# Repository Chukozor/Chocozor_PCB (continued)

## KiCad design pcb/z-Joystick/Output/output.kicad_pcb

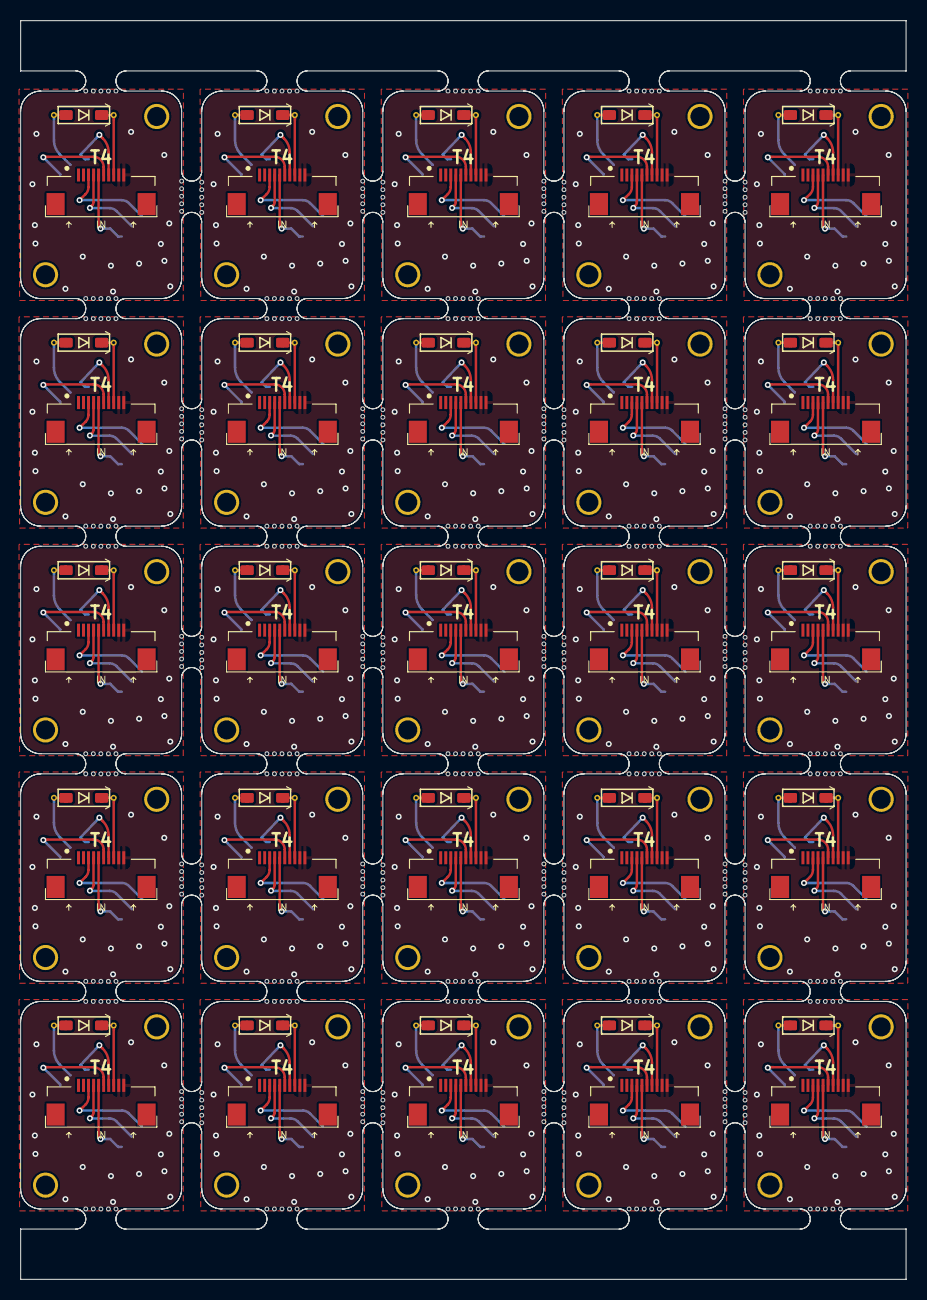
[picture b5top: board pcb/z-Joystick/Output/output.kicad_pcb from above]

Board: 2 copper layers, 88.0 x 125.1 mm, 575 parts (0 on the bottom side), 200 nets.

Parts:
D32, D32#2, D32#3, D32#4, D32#5, D32#6, D32#7, D32#8, D32#9, D32#10, D32#11, D32#12, D32#13, D32#14, D32#15, D32#16, D32#17, D32#18, D32#19, D32#20, D32#21, D32#22, D32#23, D32#24, D32#25: 1N4148; SMD_SOD_123-stencil
KiKit_MB_1_1, KiKit_MB_1_2, KiKit_MB_1_3, KiKit_MB_1_4, KiKit_MB_1_5, KiKit_MB_2_1, KiKit_MB_2_2, KiKit_MB_2_3, KiKit_MB_2_4, KiKit_MB_2_5, KiKit_MB_3_1, KiKit_MB_3_2, KiKit_MB_3_3, KiKit_MB_3_4, KiKit_MB_3_5, KiKit_MB_4_1, KiKit_MB_4_2, KiKit_MB_4_3, KiKit_MB_4_4, KiKit_MB_4_5, KiKit_MB_5_1, KiKit_MB_5_2, KiKit_MB_5_3, KiKit_MB_5_4, KiKit_MB_5_5, KiKit_MB_6_1, KiKit_MB_6_2, KiKit_MB_6_3, KiKit_MB_6_4, KiKit_MB_6_5, KiKit_MB_7_1, KiKit_MB_7_2, KiKit_MB_7_3, KiKit_MB_7_4, KiKit_MB_7_5, KiKit_MB_8_1, KiKit_MB_8_2, KiKit_MB_8_3, KiKit_MB_8_4, KiKit_MB_8_5, KiKit_MB_9_1, KiKit_MB_9_2, KiKit_MB_9_3, KiKit_MB_9_4, KiKit_MB_9_5, KiKit_MB_10_1, KiKit_MB_10_2, KiKit_MB_10_3, KiKit_MB_10_4, KiKit_MB_10_5, KiKit_MB_11_1, KiKit_MB_11_2, KiKit_MB_11_3, KiKit_MB_11_4, KiKit_MB_11_5, KiKit_MB_12_1, KiKit_MB_12_2, KiKit_MB_12_3, KiKit_MB_12_4, KiKit_MB_12_5, KiKit_MB_13_1, KiKit_MB_13_2, KiKit_MB_13_3, KiKit_MB_13_4, KiKit_MB_13_5, KiKit_MB_14_1, KiKit_MB_14_2, KiKit_MB_14_3, KiKit_MB_14_4, KiKit_MB_14_5, KiKit_MB_15_1, KiKit_MB_15_2, KiKit_MB_15_3, KiKit_MB_15_4, KiKit_MB_15_5, KiKit_MB_16_1, KiKit_MB_16_2, KiKit_MB_16_3, KiKit_MB_16_4, KiKit_MB_16_5, KiKit_MB_17_1, KiKit_MB_17_2, KiKit_MB_17_3, KiKit_MB_17_4, KiKit_MB_17_5, KiKit_MB_18_1, KiKit_MB_18_2, KiKit_MB_18_3, KiKit_MB_18_4, KiKit_MB_18_5, KiKit_MB_19_1, KiKit_MB_19_2, KiKit_MB_19_3, KiKit_MB_19_4, KiKit_MB_19_5, KiKit_MB_20_1, KiKit_MB_20_2, KiKit_MB_20_3, KiKit_MB_20_4, KiKit_MB_20_5, KiKit_MB_21_1, KiKit_MB_21_2, KiKit_MB_21_3, KiKit_MB_21_4, KiKit_MB_21_5, KiKit_MB_22_1, KiKit_MB_22_2, KiKit_MB_22_3, KiKit_MB_22_4, KiKit_MB_22_5, KiKit_MB_23_1, KiKit_MB_23_2, KiKit_MB_23_3, KiKit_MB_23_4, KiKit_MB_23_5, KiKit_MB_24_1, KiKit_MB_24_2, KiKit_MB_24_3, KiKit_MB_24_4, KiKit_MB_24_5, KiKit_MB_25_1, KiKit_MB_25_2, KiKit_MB_25_3, KiKit_MB_25_4, KiKit_MB_25_5, KiKit_MB_26_1, KiKit_MB_26_2, KiKit_MB_26_3, KiKit_MB_26_4, KiKit_MB_26_5, KiKit_MB_27_1, KiKit_MB_27_2, KiKit_MB_27_3, KiKit_MB_27_4, KiKit_MB_27_5, KiKit_MB_28_1, KiKit_MB_28_2, KiKit_MB_28_3, KiKit_MB_28_4, KiKit_MB_28_5, KiKit_MB_29_1, KiKit_MB_29_2, KiKit_MB_29_3, KiKit_MB_29_4, KiKit_MB_29_5, KiKit_MB_30_1, KiKit_MB_30_2, KiKit_MB_30_3, KiKit_MB_30_4, KiKit_MB_30_5, KiKit_MB_31_1, KiKit_MB_31_2, KiKit_MB_31_3, KiKit_MB_31_4, KiKit_MB_31_5, KiKit_MB_32_1, KiKit_MB_32_2, KiKit_MB_32_3, KiKit_MB_32_4, KiKit_MB_32_5, KiKit_MB_33_1, KiKit_MB_33_2, KiKit_MB_33_3, KiKit_MB_33_4, KiKit_MB_33_5, KiKit_MB_34_1, KiKit_MB_34_2, KiKit_MB_34_3, KiKit_MB_34_4, KiKit_MB_34_5, KiKit_MB_35_1, KiKit_MB_35_2, KiKit_MB_35_3, KiKit_MB_35_4, KiKit_MB_35_5, KiKit_MB_36_1, KiKit_MB_36_2, KiKit_MB_36_3, KiKit_MB_36_4, KiKit_MB_36_5, KiKit_MB_37_1, KiKit_MB_37_2, KiKit_MB_37_3, KiKit_MB_37_4, KiKit_MB_37_5, KiKit_MB_38_1, KiKit_MB_38_2, KiKit_MB_38_3, KiKit_MB_38_4, KiKit_MB_38_5, KiKit_MB_39_1, KiKit_MB_39_2, KiKit_MB_39_3, KiKit_MB_39_4, KiKit_MB_39_5, KiKit_MB_40_1, KiKit_MB_40_2, KiKit_MB_40_3, KiKit_MB_40_4, KiKit_MB_40_5, KiKit_MB_41_1, KiKit_MB_41_2, KiKit_MB_41_3, KiKit_MB_41_4, KiKit_MB_41_5, KiKit_MB_42_1, KiKit_MB_42_2, KiKit_MB_42_3, KiKit_MB_42_4, KiKit_MB_42_5, KiKit_MB_43_1, KiKit_MB_43_2, KiKit_MB_43_3, KiKit_MB_43_4, KiKit_MB_43_5, KiKit_MB_44_1, KiKit_MB_44_2, KiKit_MB_44_3, KiKit_MB_44_4, KiKit_MB_44_5, KiKit_MB_45_1, KiKit_MB_45_2, KiKit_MB_45_3, KiKit_MB_45_4, KiKit_MB_45_5, KiKit_MB_46_1, KiKit_MB_46_2, KiKit_MB_46_3, KiKit_MB_46_4, KiKit_MB_46_5, KiKit_MB_47_1, KiKit_MB_47_2, KiKit_MB_47_3, KiKit_MB_47_4, KiKit_MB_47_5, KiKit_MB_48_1, KiKit_MB_48_2, KiKit_MB_48_3, KiKit_MB_48_4, KiKit_MB_48_5, KiKit_MB_49_1, KiKit_MB_49_2, KiKit_MB_49_3, KiKit_MB_49_4, KiKit_MB_49_5, KiKit_MB_50_1, KiKit_MB_50_2, KiKit_MB_50_3, KiKit_MB_50_4, KiKit_MB_50_5, KiKit_MB_51_1, KiKit_MB_51_2, KiKit_MB_51_3, KiKit_MB_51_4, KiKit_MB_51_5, KiKit_MB_52_1, KiKit_MB_52_2, KiKit_MB_52_3, KiKit_MB_52_4, KiKit_MB_52_5, KiKit_MB_53_1, KiKit_MB_53_2, KiKit_MB_53_3, KiKit_MB_53_4, KiKit_MB_53_5, KiKit_MB_54_1, KiKit_MB_54_2, KiKit_MB_54_3, KiKit_MB_54_4, KiKit_MB_54_5, KiKit_MB_55_1, KiKit_MB_55_2, KiKit_MB_55_3, KiKit_MB_55_4, KiKit_MB_55_5, KiKit_MB_56_1, KiKit_MB_56_2, KiKit_MB_56_3, KiKit_MB_56_4, KiKit_MB_56_5, KiKit_MB_57_1, KiKit_MB_57_2, KiKit_MB_57_3, KiKit_MB_57_4, KiKit_MB_57_5, KiKit_MB_58_1, KiKit_MB_58_2, KiKit_MB_58_3, KiKit_MB_58_4, KiKit_MB_58_5, KiKit_MB_59_1, KiKit_MB_59_2, KiKit_MB_59_3, KiKit_MB_59_4, KiKit_MB_59_5, KiKit_MB_60_1, KiKit_MB_60_2, KiKit_MB_60_3, KiKit_MB_60_4, KiKit_MB_60_5, KiKit_MB_61_1, KiKit_MB_61_2, KiKit_MB_61_3, KiKit_MB_61_4, KiKit_MB_61_5, KiKit_MB_62_1, KiKit_MB_62_2, KiKit_MB_62_3, KiKit_MB_62_4, KiKit_MB_62_5, KiKit_MB_63_1, KiKit_MB_63_2, KiKit_MB_63_3, KiKit_MB_63_4, KiKit_MB_63_5, KiKit_MB_64_1, KiKit_MB_64_2, KiKit_MB_64_3, KiKit_MB_64_4, KiKit_MB_64_5, KiKit_MB_65_1, KiKit_MB_65_2, KiKit_MB_65_3, KiKit_MB_65_4, KiKit_MB_65_5, KiKit_MB_66_1, KiKit_MB_66_2, KiKit_MB_66_3, KiKit_MB_66_4, KiKit_MB_66_5, KiKit_MB_67_1, KiKit_MB_67_2, KiKit_MB_67_3, KiKit_MB_67_4, KiKit_MB_67_5, KiKit_MB_68_1, KiKit_MB_68_2, KiKit_MB_68_3, KiKit_MB_68_4, KiKit_MB_68_5, KiKit_MB_69_1, KiKit_MB_69_2, KiKit_MB_69_3, KiKit_MB_69_4, KiKit_MB_69_5, KiKit_MB_70_1, KiKit_MB_70_2, KiKit_MB_70_3, KiKit_MB_70_4, KiKit_MB_70_5, KiKit_MB_71_1, KiKit_MB_71_2, KiKit_MB_71_3, KiKit_MB_71_4, KiKit_MB_71_5, KiKit_MB_72_1, KiKit_MB_72_2, KiKit_MB_72_3, KiKit_MB_72_4, KiKit_MB_72_5, KiKit_MB_73_1, KiKit_MB_73_2, KiKit_MB_73_3, KiKit_MB_73_4, KiKit_MB_73_5, KiKit_MB_74_1, KiKit_MB_74_2, KiKit_MB_74_3, KiKit_MB_74_4, KiKit_MB_74_5, KiKit_MB_75_1, KiKit_MB_75_2, KiKit_MB_75_3, KiKit_MB_75_4, KiKit_MB_75_5, KiKit_MB_76_1, KiKit_MB_76_2, KiKit_MB_76_3, KiKit_MB_76_4, KiKit_MB_76_5, KiKit_MB_77_1, KiKit_MB_77_2, KiKit_MB_77_3, KiKit_MB_77_4, KiKit_MB_77_5, KiKit_MB_78_1, KiKit_MB_78_2, KiKit_MB_78_3, KiKit_MB_78_4, KiKit_MB_78_5, KiKit_MB_79_1, KiKit_MB_79_2, KiKit_MB_79_3, KiKit_MB_79_4, KiKit_MB_79_5, KiKit_MB_80_1, KiKit_MB_80_2, KiKit_MB_80_3, KiKit_MB_80_4, KiKit_MB_80_5, KiKit_MB_81_1, KiKit_MB_81_2, KiKit_MB_81_3, KiKit_MB_81_4, KiKit_MB_81_5, KiKit_MB_82_1, KiKit_MB_82_2, KiKit_MB_82_3, KiKit_MB_82_4, KiKit_MB_82_5, KiKit_MB_83_1, KiKit_MB_83_2, KiKit_MB_83_3, KiKit_MB_83_4, KiKit_MB_83_5, KiKit_MB_84_1, KiKit_MB_84_2, KiKit_MB_84_3, KiKit_MB_84_4, KiKit_MB_84_5, KiKit_MB_85_1, KiKit_MB_85_2, KiKit_MB_85_3, KiKit_MB_85_4, KiKit_MB_85_5, KiKit_MB_86_1, KiKit_MB_86_2, KiKit_MB_86_3, KiKit_MB_86_4, KiKit_MB_86_5, KiKit_MB_87_1, KiKit_MB_87_2, KiKit_MB_87_3, KiKit_MB_87_4, KiKit_MB_87_5, KiKit_MB_88_1, KiKit_MB_88_2, KiKit_MB_88_3, KiKit_MB_88_4, KiKit_MB_88_5, KiKit_MB_89_1, KiKit_MB_89_2, KiKit_MB_89_3, KiKit_MB_89_4, KiKit_MB_89_5, KiKit_MB_90_1, KiKit_MB_90_2, KiKit_MB_90_3, KiKit_MB_90_4, KiKit_MB_90_5: NPTH
M1.6-9, M1.6-9#2, M1.6-9#3, M1.6-9#4, M1.6-9#5, M1.6-9#6, M1.6-9#7, M1.6-9#8, M1.6-9#9, M1.6-9#10, M1.6-9#11, M1.6-9#12, M1.6-9#13, M1.6-9#14, M1.6-9#15, M1.6-9#16, M1.6-9#17, M1.6-9#18, M1.6-9#19, M1.6-9#20, M1.6-9#21, M1.6-9#22, M1.6-9#23, M1.6-9#24, M1.6-9#25, M1.6-10, M1.6-10#2, M1.6-10#3, M1.6-10#4, M1.6-10#5, M1.6-10#6, M1.6-10#7, M1.6-10#8, M1.6-10#9, M1.6-10#10, M1.6-10#11, M1.6-10#12, M1.6-10#13, M1.6-10#14, M1.6-10#15, M1.6-10#16, M1.6-10#17, M1.6-10#18, M1.6-10#19, M1.6-10#20, M1.6-10#21, M1.6-10#22, M1.6-10#23, M1.6-10#24, M1.6-10#25: MountingHoleM1.6; Mounting-hole-M1.6
S2, S2#2, S2#3, S2#4, S2#5, S2#6, S2#7, S2#8, S2#9, S2#10, S2#11, S2#12, S2#13, S2#14, S2#15, S2#16, S2#17, S2#18, S2#19, S2#20, S2#21, S2#22, S2#23, S2#24, S2#25: 5-ways-switches(joystick); QUE-JOYSTICK-UNE-FACE(non reversible-pourvA)
T4, T4#2, T4#3, T4#4, T4#5, T4#6, T4#7, T4#8, T4#9, T4#10, T4#11, T4#12, T4#13, T4#14, T4#15, T4#16, T4#17, T4#18, T4#19, T4#20, T4#21, T4#22, T4#23, T4#24, T4#25: FPC_8pins_SPECIAL-thumbs; FPC_10p-reversible-QUE-JOYSTICK-IN(non reversible-vA)

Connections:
Board_0-GND-joystick: T4#23.9 (9_GND), T4#23.10 (10_GND)
Board_0-Net-(D32-A): D32#4.2 (A), S2#9.5 (COM)
Board_0-Net-(D32-K): D32#4.1 (K), T4#23.8 (8_ROW5-(COM))
Board_0-Net-(S2-A): S2#9.1 (A), T4#23.5 (5_COL4)
Board_0-Net-(S2-B): S2#9.4 (B), T4#23.6 (6_COL3)
Board_0-Net-(S2-C): S2#9.3 (C), T4#23.3 (3_COL1)
Board_0-Net-(S2-CENTER): S2#9.2 (CENTER), T4#23.4 (4_COL2)
Board_0-Net-(S2-D): S2#9.6 (D), T4#23.7 (7_COL0)
Board_1-GND-joystick: T4#24.9 (9_GND), T4#24.10 (10_GND)
Board_1-Net-(D32-A): D32#14.2 (A), S2#21.5 (COM)
Board_1-Net-(D32-K): D32#14.1 (K), T4#24.8 (8_ROW5-(COM))
Board_1-Net-(S2-A): S2#21.1 (A), T4#24.5 (5_COL4)
Board_1-Net-(S2-B): S2#21.4 (B), T4#24.6 (6_COL3)
Board_1-Net-(S2-C): S2#21.3 (C), T4#24.3 (3_COL1)
Board_1-Net-(S2-CENTER): S2#21.2 (CENTER), T4#24.4 (4_COL2)
Board_1-Net-(S2-D): S2#21.6 (D), T4#24.7 (7_COL0)
Board_2-GND-joystick: T4#7.9 (9_GND), T4#7.10 (10_GND)
Board_2-Net-(D32-A): D32.2 (A), S2#6.5 (COM)
Board_2-Net-(D32-K): D32.1 (K), T4#7.8 (8_ROW5-(COM))
Board_2-Net-(S2-A): S2#6.1 (A), T4#7.5 (5_COL4)
Board_2-Net-(S2-B): S2#6.4 (B), T4#7.6 (6_COL3)
Board_2-Net-(S2-C): S2#6.3 (C), T4#7.3 (3_COL1)
Board_2-Net-(S2-CENTER): S2#6.2 (CENTER), T4#7.4 (4_COL2)
Board_2-Net-(S2-D): S2#6.6 (D), T4#7.7 (7_COL0)
Board_3-GND-joystick: T4#18.9 (9_GND), T4#18.10 (10_GND)
Board_3-Net-(D32-A): D32#17.2 (A), S2.5 (COM)
Board_3-Net-(D32-K): D32#17.1 (K), T4#18.8 (8_ROW5-(COM))
Board_3-Net-(S2-A): S2.1 (A), T4#18.5 (5_COL4)
Board_3-Net-(S2-B): S2.4 (B), T4#18.6 (6_COL3)
Board_3-Net-(S2-C): S2.3 (C), T4#18.3 (3_COL1)
Board_3-Net-(S2-CENTER): S2.2 (CENTER), T4#18.4 (4_COL2)
Board_3-Net-(S2-D): S2.6 (D), T4#18.7 (7_COL0)
Board_4-GND-joystick: T4#5.9 (9_GND), T4#5.10 (10_GND)
Board_4-Net-(D32-A): D32#24.2 (A), S2#17.5 (COM)
Board_4-Net-(D32-K): D32#24.1 (K), T4#5.8 (8_ROW5-(COM))
Board_4-Net-(S2-A): S2#17.1 (A), T4#5.5 (5_COL4)
Board_4-Net-(S2-B): S2#17.4 (B), T4#5.6 (6_COL3)
Board_4-Net-(S2-C): S2#17.3 (C), T4#5.3 (3_COL1)
Board_4-Net-(S2-CENTER): S2#17.2 (CENTER), T4#5.4 (4_COL2)
Board_4-Net-(S2-D): S2#17.6 (D), T4#5.7 (7_COL0)
Board_5-GND-joystick: T4#3.9 (9_GND), T4#3.10 (10_GND)
Board_5-Net-(D32-A): D32#19.2 (A), S2#16.5 (COM)
Board_5-Net-(D32-K): D32#19.1 (K), T4#3.8 (8_ROW5-(COM))
Board_5-Net-(S2-A): S2#16.1 (A), T4#3.5 (5_COL4)
Board_5-Net-(S2-B): S2#16.4 (B), T4#3.6 (6_COL3)
Board_5-Net-(S2-C): S2#16.3 (C), T4#3.3 (3_COL1)
Board_5-Net-(S2-CENTER): S2#16.2 (CENTER), T4#3.4 (4_COL2)
Board_5-Net-(S2-D): S2#16.6 (D), T4#3.7 (7_COL0)
Board_6-GND-joystick: T4#12.9 (9_GND), T4#12.10 (10_GND)
Board_6-Net-(D32-A): D32#6.2 (A), S2#25.5 (COM)
Board_6-Net-(D32-K): D32#6.1 (K), T4#12.8 (8_ROW5-(COM))
Board_6-Net-(S2-A): S2#25.1 (A), T4#12.5 (5_COL4)
Board_6-Net-(S2-B): S2#25.4 (B), T4#12.6 (6_COL3)
Board_6-Net-(S2-C): S2#25.3 (C), T4#12.3 (3_COL1)
Board_6-Net-(S2-CENTER): S2#25.2 (CENTER), T4#12.4 (4_COL2)
Board_6-Net-(S2-D): S2#25.6 (D), T4#12.7 (7_COL0)
Board_7-GND-joystick: T4#2.9 (9_GND), T4#2.10 (10_GND)
Board_7-Net-(D32-A): D32#7.2 (A), S2#3.5 (COM)
Board_7-Net-(D32-K): D32#7.1 (K), T4#2.8 (8_ROW5-(COM))
Board_7-Net-(S2-A): S2#3.1 (A), T4#2.5 (5_COL4)
Board_7-Net-(S2-B): S2#3.4 (B), T4#2.6 (6_COL3)
Board_7-Net-(S2-C): S2#3.3 (C), T4#2.3 (3_COL1)
Board_7-Net-(S2-CENTER): S2#3.2 (CENTER), T4#2.4 (4_COL2)
Board_7-Net-(S2-D): S2#3.6 (D), T4#2.7 (7_COL0)
Board_8-GND-joystick: T4#13.9 (9_GND), T4#13.10 (10_GND)
Board_8-Net-(D32-A): D32#2.2 (A), S2#14.5 (COM)
Board_8-Net-(D32-K): D32#2.1 (K), T4#13.8 (8_ROW5-(COM))
Board_8-Net-(S2-A): S2#14.1 (A), T4#13.5 (5_COL4)
Board_8-Net-(S2-B): S2#14.4 (B), T4#13.6 (6_COL3)
Board_8-Net-(S2-C): S2#14.3 (C), T4#13.3 (3_COL1)
Board_8-Net-(S2-CENTER): S2#14.2 (CENTER), T4#13.4 (4_COL2)
Board_8-Net-(S2-D): S2#14.6 (D), T4#13.7 (7_COL0)
Board_9-GND-joystick: T4#6.9 (9_GND), T4#6.10 (10_GND)
Board_9-Net-(D32-A): D32#13.2 (A), S2#19.5 (COM)
Board_9-Net-(D32-K): D32#13.1 (K), T4#6.8 (8_ROW5-(COM))
Board_9-Net-(S2-A): S2#19.1 (A), T4#6.5 (5_COL4)
Board_9-Net-(S2-B): S2#19.4 (B), T4#6.6 (6_COL3)
Board_9-Net-(S2-C): S2#19.3 (C), T4#6.3 (3_COL1)
Board_9-Net-(S2-CENTER): S2#19.2 (CENTER), T4#6.4 (4_COL2)
Board_9-Net-(S2-D): S2#19.6 (D), T4#6.7 (7_COL0)
Board_10-GND-joystick: T4.9 (9_GND), T4.10 (10_GND)
Board_10-Net-(D32-A): D32#21.2 (A), S2#12.5 (COM)
Board_10-Net-(D32-K): D32#21.1 (K), T4.8 (8_ROW5-(COM))
Board_10-Net-(S2-A): S2#12.1 (A), T4.5 (5_COL4)
Board_10-Net-(S2-B): S2#12.4 (B), T4.6 (6_COL3)
Board_10-Net-(S2-C): S2#12.3 (C), T4.3 (3_COL1)
Board_10-Net-(S2-CENTER): S2#12.2 (CENTER), T4.4 (4_COL2)
Board_10-Net-(S2-D): S2#12.6 (D), T4.7 (7_COL0)
Board_11-GND-joystick: T4#10.9 (9_GND), T4#10.10 (10_GND)
Board_11-Net-(D32-A): D32#22.2 (A), S2#8.5 (COM)
Board_11-Net-(D32-K): D32#22.1 (K), T4#10.8 (8_ROW5-(COM))
Board_11-Net-(S2-A): S2#8.1 (A), T4#10.5 (5_COL4)
Board_11-Net-(S2-B): S2#8.4 (B), T4#10.6 (6_COL3)
Board_11-Net-(S2-C): S2#8.3 (C), T4#10.3 (3_COL1)
Board_11-Net-(S2-CENTER): S2#8.2 (CENTER), T4#10.4 (4_COL2)
Board_11-Net-(S2-D): S2#8.6 (D), T4#10.7 (7_COL0)
Board_12-GND-joystick: T4#21.9 (9_GND), T4#21.10 (10_GND)
Board_12-Net-(D32-A): D32#9.2 (A), S2#20.5 (COM)
Board_12-Net-(D32-K): D32#9.1 (K), T4#21.8 (8_ROW5-(COM))
Board_12-Net-(S2-A): S2#20.1 (A), T4#21.5 (5_COL4)
Board_12-Net-(S2-B): S2#20.4 (B), T4#21.6 (6_COL3)
Board_12-Net-(S2-C): S2#20.3 (C), T4#21.3 (3_COL1)
Board_12-Net-(S2-CENTER): S2#20.2 (CENTER), T4#21.4 (4_COL2)
Board_12-Net-(S2-D): S2#20.6 (D), T4#21.7 (7_COL0)
Board_13-GND-joystick: T4#20.9 (9_GND), T4#20.10 (10_GND)
Board_13-Net-(D32-A): D32#12.2 (A), S2#4.5 (COM)
Board_13-Net-(D32-K): D32#12.1 (K), T4#20.8 (8_ROW5-(COM))
Board_13-Net-(S2-A): S2#4.1 (A), T4#20.5 (5_COL4)
Board_13-Net-(S2-B): S2#4.4 (B), T4#20.6 (6_COL3)
Board_13-Net-(S2-C): S2#4.3 (C), T4#20.3 (3_COL1)
Board_13-Net-(S2-CENTER): S2#4.2 (CENTER), T4#20.4 (4_COL2)
Board_13-Net-(S2-D): S2#4.6 (D), T4#20.7 (7_COL0)
Board_14-GND-joystick: T4#11.9 (9_GND), T4#11.10 (10_GND)
Board_14-Net-(D32-A): D32#3.2 (A), S2#18.5 (COM)
Board_14-Net-(D32-K): D32#3.1 (K), T4#11.8 (8_ROW5-(COM))
Board_14-Net-(S2-A): S2#18.1 (A), T4#11.5 (5_COL4)
Board_14-Net-(S2-B): S2#18.4 (B), T4#11.6 (6_COL3)
Board_14-Net-(S2-C): S2#18.3 (C), T4#11.3 (3_COL1)
Board_14-Net-(S2-CENTER): S2#18.2 (CENTER), T4#11.4 (4_COL2)
Board_14-Net-(S2-D): S2#18.6 (D), T4#11.7 (7_COL0)
Board_15-GND-joystick: T4#8.9 (9_GND), T4#8.10 (10_GND)
Board_15-Net-(D32-A): D32#5.2 (A), S2#10.5 (COM)
Board_15-Net-(D32-K): D32#5.1 (K), T4#8.8 (8_ROW5-(COM))
Board_15-Net-(S2-A): S2#10.1 (A), T4#8.5 (5_COL4)
Board_15-Net-(S2-B): S2#10.4 (B), T4#8.6 (6_COL3)
Board_15-Net-(S2-C): S2#10.3 (C), T4#8.3 (3_COL1)
Board_15-Net-(S2-CENTER): S2#10.2 (CENTER), T4#8.4 (4_COL2)
Board_15-Net-(S2-D): S2#10.6 (D), T4#8.7 (7_COL0)
Board_16-GND-joystick: T4#22.9 (9_GND), T4#22.10 (10_GND)
Board_16-Net-(D32-A): D32#16.2 (A), S2#13.5 (COM)
Board_16-Net-(D32-K): D32#16.1 (K), T4#22.8 (8_ROW5-(COM))
Board_16-Net-(S2-A): S2#13.1 (A), T4#22.5 (5_COL4)
Board_16-Net-(S2-B): S2#13.4 (B), T4#22.6 (6_COL3)
Board_16-Net-(S2-C): S2#13.3 (C), T4#22.3 (3_COL1)
Board_16-Net-(S2-CENTER): S2#13.2 (CENTER), T4#22.4 (4_COL2)
Board_16-Net-(S2-D): S2#13.6 (D), T4#22.7 (7_COL0)
Board_17-GND-joystick: T4#17.9 (9_GND), T4#17.10 (10_GND)
Board_17-Net-(D32-A): D32#15.2 (A), S2#5.5 (COM)
Board_17-Net-(D32-K): D32#15.1 (K), T4#17.8 (8_ROW5-(COM))
Board_17-Net-(S2-A): S2#5.1 (A), T4#17.5 (5_COL4)
Board_17-Net-(S2-B): S2#5.4 (B), T4#17.6 (6_COL3)
Board_17-Net-(S2-C): S2#5.3 (C), T4#17.3 (3_COL1)
Board_17-Net-(S2-CENTER): S2#5.2 (CENTER), T4#17.4 (4_COL2)
Board_17-Net-(S2-D): S2#5.6 (D), T4#17.7 (7_COL0)
Board_18-GND-joystick: T4#25.9 (9_GND), T4#25.10 (10_GND)
Board_18-Net-(D32-A): D32#23.2 (A), S2#7.5 (COM)
Board_18-Net-(D32-K): D32#23.1 (K), T4#25.8 (8_ROW5-(COM))
Board_18-Net-(S2-A): S2#7.1 (A), T4#25.5 (5_COL4)
Board_18-Net-(S2-B): S2#7.4 (B), T4#25.6 (6_COL3)
Board_18-Net-(S2-C): S2#7.3 (C), T4#25.3 (3_COL1)
Board_18-Net-(S2-CENTER): S2#7.2 (CENTER), T4#25.4 (4_COL2)
Board_18-Net-(S2-D): S2#7.6 (D), T4#25.7 (7_COL0)
Board_19-GND-joystick: T4#15.9 (9_GND), T4#15.10 (10_GND)
Board_19-Net-(D32-A): D32#8.2 (A), S2#24.5 (COM)
Board_19-Net-(D32-K): D32#8.1 (K), T4#15.8 (8_ROW5-(COM))
Board_19-Net-(S2-A): S2#24.1 (A), T4#15.5 (5_COL4)
Board_19-Net-(S2-B): S2#24.4 (B), T4#15.6 (6_COL3)
Board_19-Net-(S2-C): S2#24.3 (C), T4#15.3 (3_COL1)
Board_19-Net-(S2-CENTER): S2#24.2 (CENTER), T4#15.4 (4_COL2)
Board_19-Net-(S2-D): S2#24.6 (D), T4#15.7 (7_COL0)
Board_20-GND-joystick: T4#14.9 (9_GND), T4#14.10 (10_GND)
Board_20-Net-(D32-A): D32#11.2 (A), S2#2.5 (COM)
Board_20-Net-(D32-K): D32#11.1 (K), T4#14.8 (8_ROW5-(COM))
Board_20-Net-(S2-A): S2#2.1 (A), T4#14.5 (5_COL4)
Board_20-Net-(S2-B): S2#2.4 (B), T4#14.6 (6_COL3)
Board_20-Net-(S2-C): S2#2.3 (C), T4#14.3 (3_COL1)
Board_20-Net-(S2-CENTER): S2#2.2 (CENTER), T4#14.4 (4_COL2)
Board_20-Net-(S2-D): S2#2.6 (D), T4#14.7 (7_COL0)
Board_21-GND-joystick: T4#4.9 (9_GND), T4#4.10 (10_GND)
Board_21-Net-(D32-A): D32#25.2 (A), S2#22.5 (COM)
Board_21-Net-(D32-K): D32#25.1 (K), T4#4.8 (8_ROW5-(COM))
Board_21-Net-(S2-A): S2#22.1 (A), T4#4.5 (5_COL4)
Board_21-Net-(S2-B): S2#22.4 (B), T4#4.6 (6_COL3)
Board_21-Net-(S2-C): S2#22.3 (C), T4#4.3 (3_COL1)
Board_21-Net-(S2-CENTER): S2#22.2 (CENTER), T4#4.4 (4_COL2)
Board_21-Net-(S2-D): S2#22.6 (D), T4#4.7 (7_COL0)
Board_22-GND-joystick: T4#19.9 (9_GND), T4#19.10 (10_GND)
Board_22-Net-(D32-A): D32#10.2 (A), S2#11.5 (COM)
Board_22-Net-(D32-K): D32#10.1 (K), T4#19.8 (8_ROW5-(COM))
Board_22-Net-(S2-A): S2#11.1 (A), T4#19.5 (5_COL4)
Board_22-Net-(S2-B): S2#11.4 (B), T4#19.6 (6_COL3)
Board_22-Net-(S2-C): S2#11.3 (C), T4#19.3 (3_COL1)
Board_22-Net-(S2-CENTER): S2#11.2 (CENTER), T4#19.4 (4_COL2)
Board_22-Net-(S2-D): S2#11.6 (D), T4#19.7 (7_COL0)
Board_23-GND-joystick: T4#16.9 (9_GND), T4#16.10 (10_GND)
Board_23-Net-(D32-A): D32#20.2 (A), S2#23.5 (COM)
Board_23-Net-(D32-K): D32#20.1 (K), T4#16.8 (8_ROW5-(COM))
Board_23-Net-(S2-A): S2#23.1 (A), T4#16.5 (5_COL4)
Board_23-Net-(S2-B): S2#23.4 (B), T4#16.6 (6_COL3)
Board_23-Net-(S2-C): S2#23.3 (C), T4#16.3 (3_COL1)
Board_23-Net-(S2-CENTER): S2#23.2 (CENTER), T4#16.4 (4_COL2)
Board_23-Net-(S2-D): S2#23.6 (D), T4#16.7 (7_COL0)
Board_24-GND-joystick: T4#9.9 (9_GND), T4#9.10 (10_GND)
Board_24-Net-(D32-A): D32#18.2 (A), S2#15.5 (COM)
Board_24-Net-(D32-K): D32#18.1 (K), T4#9.8 (8_ROW5-(COM))
Board_24-Net-(S2-A): S2#15.1 (A), T4#9.5 (5_COL4)
Board_24-Net-(S2-B): S2#15.4 (B), T4#9.6 (6_COL3)
Board_24-Net-(S2-C): S2#15.3 (C), T4#9.3 (3_COL1)
Board_24-Net-(S2-CENTER): S2#15.2 (CENTER), T4#9.4 (4_COL2)
Board_24-Net-(S2-D): S2#15.6 (D), T4#9.7 (7_COL0)

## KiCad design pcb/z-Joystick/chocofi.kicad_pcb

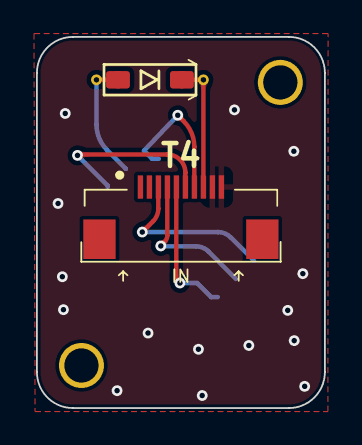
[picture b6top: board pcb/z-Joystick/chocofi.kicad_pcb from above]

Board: 2 copper layers, 16.0 x 20.6 mm, 5 parts (0 on the bottom side), 8 nets.

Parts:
D32: 1N4148; SMD_SOD_123-stencil
M1.6-9, M1.6-10: MountingHoleM1.6; Mounting-hole-M1.6
S2: 5-ways-switches(joystick); QUE-JOYSTICK-UNE-FACE(non reversible-pourvA)
T4: FPC_8pins_SPECIAL-thumbs; FPC_10p-reversible-QUE-JOYSTICK-IN(non reversible-vA)

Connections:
GND-joystick: T4.9 (9_GND), T4.10 (10_GND)
unnamed: D32.2 (A), S2.5 (COM)
unnamed: D32.1 (K), T4.8 (8_ROW5-(COM))
unnamed: S2.1 (A), T4.5 (5_COL4)
unnamed: S2.4 (B), T4.6 (6_COL3)
unnamed: S2.3 (C), T4.3 (3_COL1)
unnamed: S2.2 (CENTER), T4.4 (4_COL2)
unnamed: S2.6 (D), T4.7 (7_COL0)
